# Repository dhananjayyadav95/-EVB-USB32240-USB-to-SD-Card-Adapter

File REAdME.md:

# EVB-USB32240 USB to SD Card Adapter

An open-source hardware design for a USB to SD card adapter board based on the USB32240 controller.

## Features

- USB Type-A interface
- Micro SD card slot support
- 3.3V voltage regulation using LM3480-3.3
- Crystal oscillator for clock generation
- Status LED indicator
- SMD components for compact design

## Hardware Specifications

- **USB Interface**: USB Type-A connector
- **SD Card**: Micro SD card slot
- **Voltage Regulator**: LM3480-3.3 for 3.3V power supply
- **Crystal**: External crystal for clock generation
- **Form Factor**: Compact SMD design
- **PCB Layers**: 2-layer board (F.Cu and B.Cu)

## Key Components

- USB32240 controller in QFN-36 package
- LM3480-3.3 voltage regulator in SOT-23 package
- Various 0201, 0402 resistors and capacitors
- Status LED for operation indication
- Crystal oscillator for stable timing

## Project Structure

```
EVB-USB32240/
├── EVB-USB32240.kicad_pcb   # PCB layout file
├── EVB-USB32240.kicad_sch   # Schematic file
├── EVB-USB32240.kicad_pro   # Project file
└── EVB-USB32240-backups/    # Backup files
```

## Manufacturing

The board is designed to be manufactured using standard PCB fabrication processes:
- 2-layer PCB
- Standard FR4 material
- Components are primarily SMD for automated assembly
- Minimal via count for cost optimization

## License

This hardware design is released under MIT License

## Contributing

Contributions to improve the design are welcome. Please feel free to:
- Submit bug reports
- Propose design improvements
- Create pull requests

## Acknowledgments

- KiCad EDA for the design tools
- Contributors and reviewers

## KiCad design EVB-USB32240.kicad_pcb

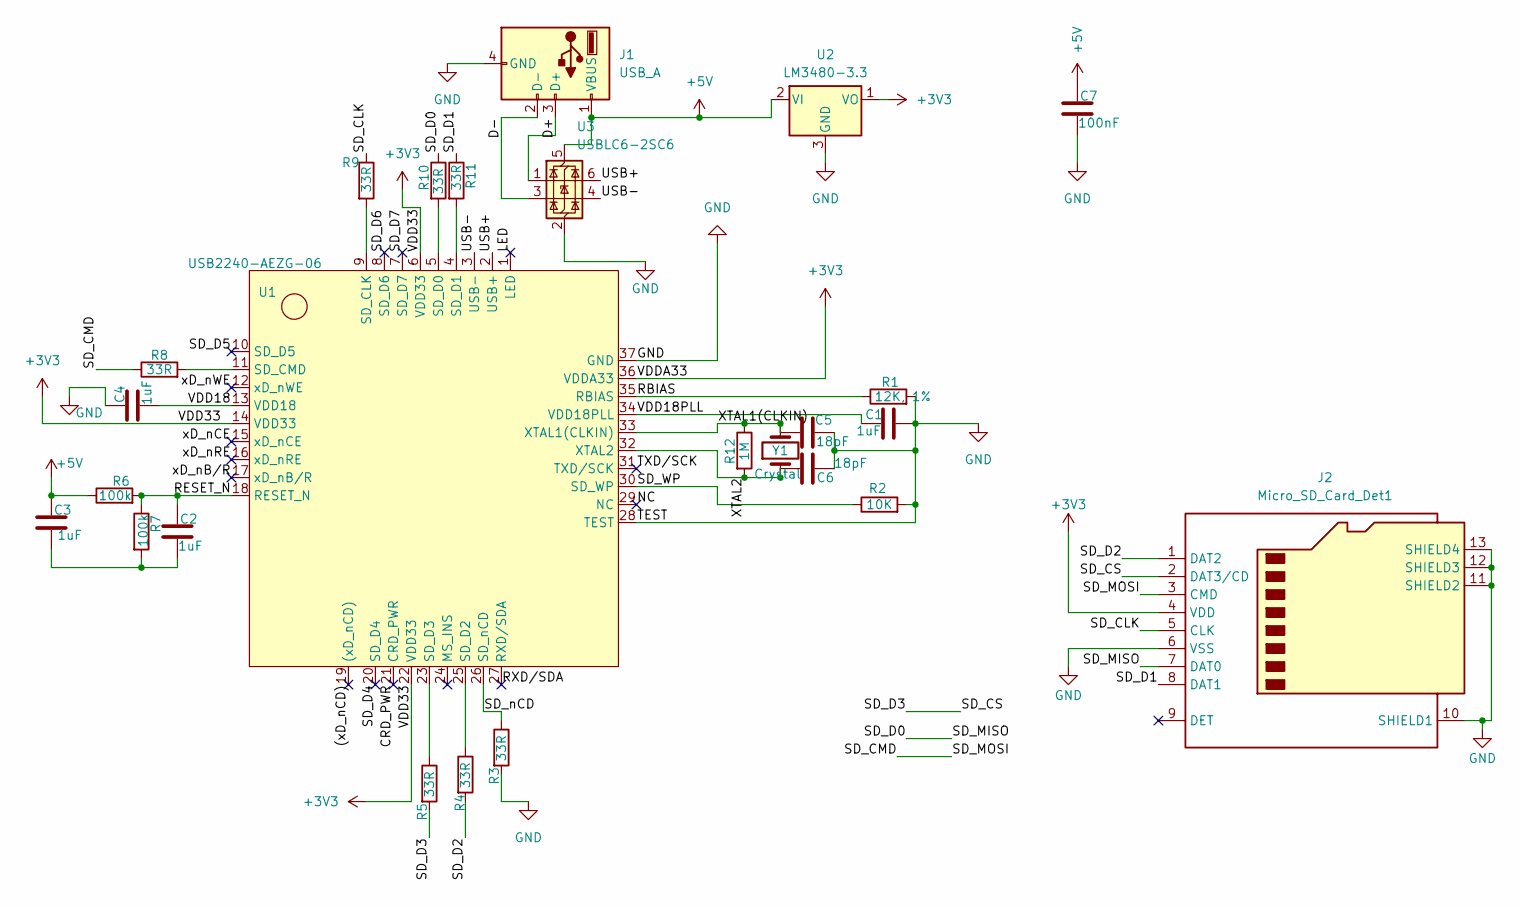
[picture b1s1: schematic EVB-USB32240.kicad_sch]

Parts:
C1: 1uF; C_0402_1005Metric
C2, C3, C4: 1uF; C_0201_0603Metric
C5, C6: 18pF; C_0402_1005Metric
C7: 100nF; C_0201_0603Metric
J1: USB_A; USB_A_Connfly_DS1095
J2: Micro_SD_Card_Det1; TF-SMD_TF-02
R1: 12K, 1%; R_0402_1005Metric
R2: 10K; R_0402_1005Metric
R3, R4, R5, R8, R9, R10, R11: 33R; R_0201_0603Metric
R6, R7: 100k; R_0201_0603Metric
R12: 1M; R_0402_1005Metric
U1: USB2240-AEZG-06; QFN-36_L6.0-W6.0-P0.50-TL-EP4.1; LCSC Part C633328
U2: LM3480-3.3; SOT-23
U3: USBLC6-2SC6; SOT-23-6
Y1: Crystal; Crystal_SMD_HC49-SD

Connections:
+3V3: J2.4 (VDD), U1.6 (VDD33), U1.14 (VDD33), U1.22 (VDD33), U1.36 (VDDA33), U2.1 (VO)
+5V: C3.1, C7.1, J1.1 (VBUS), R6.1, U2.2 (VI), U3.5 (VBUS)
/(xD_nCD): U1.19 ((xD_nCD))
/CRD_PWR: U1.21 (CRD_PWR)
/D+: J1.3 (D+), U3.1 (I/O1)
/D-: J1.2 (D-), U3.3 (I/O2)
/LED: U1.1 (LED)
/NC: U1.29 (NC)
/RBIAS: R1.1, U1.35 (RBIAS)
/RESET_N: C2.1, R6.2, R7.1, U1.18 (RESET_N)
/RXD/SDA: U1.27 (RXD/SDA)
/SD_CLK: J2.5 (CLK), R9.1
/SD_CMD: J2.3 (CMD), R8.1
/SD_CS: J2.2 (DAT3/CD), R5.2
/SD_D0: J2.7 (DAT0), R10.1
/SD_D1: J2.8 (DAT1), R11.1
/SD_D2: J2.1 (DAT2), R4.2
/SD_D4: U1.20 (SD_D4)
/SD_D5: U1.10 (SD_D5)
/SD_D6: U1.8 (SD_D6)
/SD_D7: U1.7 (SD_D7)
/SD_WP: R2.1, U1.30 (SD_WP)
/SD_nCD: R3.1, U1.26 (SD_nCD)
/TXD/SCK: U1.31 (TXD/SCK)
/USB+: U1.2 (USB+), U3.6 (I/O1)
/USB-: U1.3 (USB-), U3.4 (I/O2)
/VDD18: C4.2, U1.13 (VDD18)
/VDD18PLL: C1.1, U1.34 (VDD18PLL)
/XTAL1(CLKIN): C5.1, R12.1, U1.33 (XTAL1(CLKIN)), Y1.2
/XTAL2: C6.1, R12.2, U1.32 (XTAL2), Y1.1
/xD_nB/R: U1.17 (xD_nB/R)
/xD_nCE: U1.15 (xD_nCE)
/xD_nRE: U1.16 (xD_nRE)
/xD_nWE: U1.12 (xD_nWE)
GND: C1.2, C4.1, C5.2, C6.2, C7.2, J1.4 (GND), J2.6 (VSS), J2.10 (SHIELD1), J2.11 (SHIELD2), J2.12 (SHIELD3), J2.13 (SHIELD4), R1.2, R2.2, R3.2, U1.28 (TEST), U1.37 (GND), U2.3 (GND), U3.2 (GND)
unnamed: C2.2, C3.2, R7.2
unnamed: R9.2, U1.9 (SD_CLK)
unnamed: R8.2, U1.11 (SD_CMD)
unnamed: R10.2, U1.5 (SD_D0)
unnamed: R11.2, U1.4 (SD_D1)
unnamed: R4.1, U1.25 (SD_D2)
unnamed: R5.1, U1.23 (SD_D3)

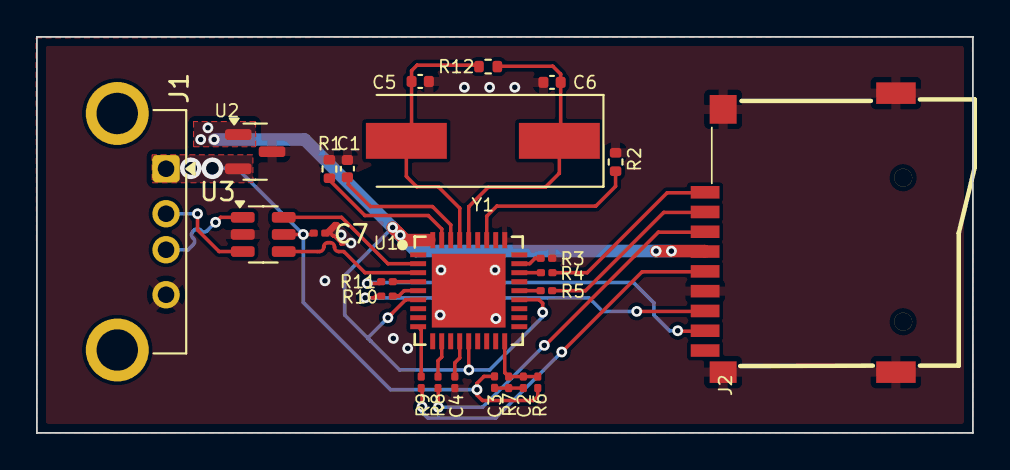
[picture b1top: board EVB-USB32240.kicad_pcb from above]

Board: 2 copper layers, 52.0 x 22.0 mm, 25 parts (0 on the bottom side), 28 nets.

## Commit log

2026-01-12 Change license to MIT and remove author section
    Updated license information from generic to MIT License and removed author section.
